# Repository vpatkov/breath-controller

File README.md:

# USB-MIDI Breath Controller

A device that converts breath pressure to MIDI data.

The mouthpiece has an adjustable valve for drain control.

The LED's brightness is proportional to the output MIDI value.
Until the USB interface is successfully configured the LED is fully on.

During initialization, the auto-zeroing of the pressure sensor
is performed. So, don't blow into the mouthpiece when
plugging the device.

The mouthpiece and the case are 3D printed from STL files
in the `3d` directory. The silicone tube is 4 mm OD and 2 mm ID.

## Software

By default, the device sends the pressure data as CC2
messages on channel 1, with maximal input and output ranges,
and linear response. These settings can be changed using the
configuration tool (in the `software` directory).

The response curve can be edited by mouse: the left button
adds and drags points, the right button removes them, and the
middle button resets the curve to default. The curve can
be arbitrary.

The input gain is applied before the curve.

Settings can be applied to the device temporary (until power
is removed) or saved permanently (in EEPROM).

The software works on Windows and Linux (both tested), and
should work on macOS.

## Technical details

The device is implemented with ATmega16U4 MCU and
MPXV4006GP pressure sensor. The MCU has hardware USB controller,
ADC, EEPROM, and other peripherals, eliminating the need of additional
chips. In firmware, [LUFA](http://www.lufa-lib.org) USB stack is used.

The pressure is sampled by ADC, averaged for 8 ms, applied auto-zero,
input gain, the response curve, and then is sent to the
host if the value differs from the previously sent one.

The response curve is implemented by a 128-byte lookup table. 
It's simple and allows arbitrary curves.

The runtime configuration is implemented with SysEx messages (see below)
from the host. The configuration tool is written in Python using
[MIDO](https://mido.readthedocs.io) and Tkinter libraries.

### SysEx messages to configure the device

- Set the MIDI channel: `F0 7D 00 XX F7` where `XX` is a MIDI
channel (1..16).

- Set the MIDI message: `F0 7D 01 XX F7` where `XX` is `00` for Control Change,
`01` for Channel Pressure, `02` for Pitch Bend Up, `03` for Pitch Bend Down.

- Set the control number: `F0 7D 02 XX F7` where `XX` is a control number (0..127).

- Set the input gain: `F0 7D 03 XX F7` where `XX` is input gain multiplied
by 10. `XX` must be in range 10..40.

- Set the response curve: `F0 7D 04 X0 X1 ... X127 F7` where
`X0 X1 ... X127` is a 128-byte lookup table. Each `Xn` must be in the range 0..127.

- Save current settings to EEPROM: `F0 7D 05 F7`.

### Preset file format

Presets used by the configuration tool are just plain text files
containing following lines:

- `midi_channel` followed by a decimal number (1..16);
- `midi_message` followed by a `control_change`, `channel_pressure`, `pitch_bend_up`,
or `pitch_bend_down`;
- `control_number` followed by a decimal number (0..127);
- `input_gain` followed by a floating point decimal number
(between 1.0 and 4.0);
- `curve` followed by a space delimited list of points `(x,y)`
where `x` and `y` are decimal numbers (0..127), assuming
linear interpolation between the points.

You can ignore some of the settings, they will not changed after loading the
preset. For example, you can create curve-only presets.

Preset must have `.preset` file extension and lie in the
`software/presets` directory.

## Programming

ATmega16U4-AU is shipped with a pre-installed USB bootloader and can be
programmed with the official
[FLIP](https://www.microchip.com/DevelopmentTools/ProductDetails/PartNO/FLIP)
software or [dfu-programmer](https://dfu-programmer.github.io/). To enter the
bootloader short HWB pin to GND during reset (there are screwdriver-compatible
pads for that on the PCB). Just in case, the PCB has pogo-compatible pads for
ISP programming. The fuses are factory default.

## License

Unless otherwise noted, this work is licensed under Creative Commons Zero 1.0.

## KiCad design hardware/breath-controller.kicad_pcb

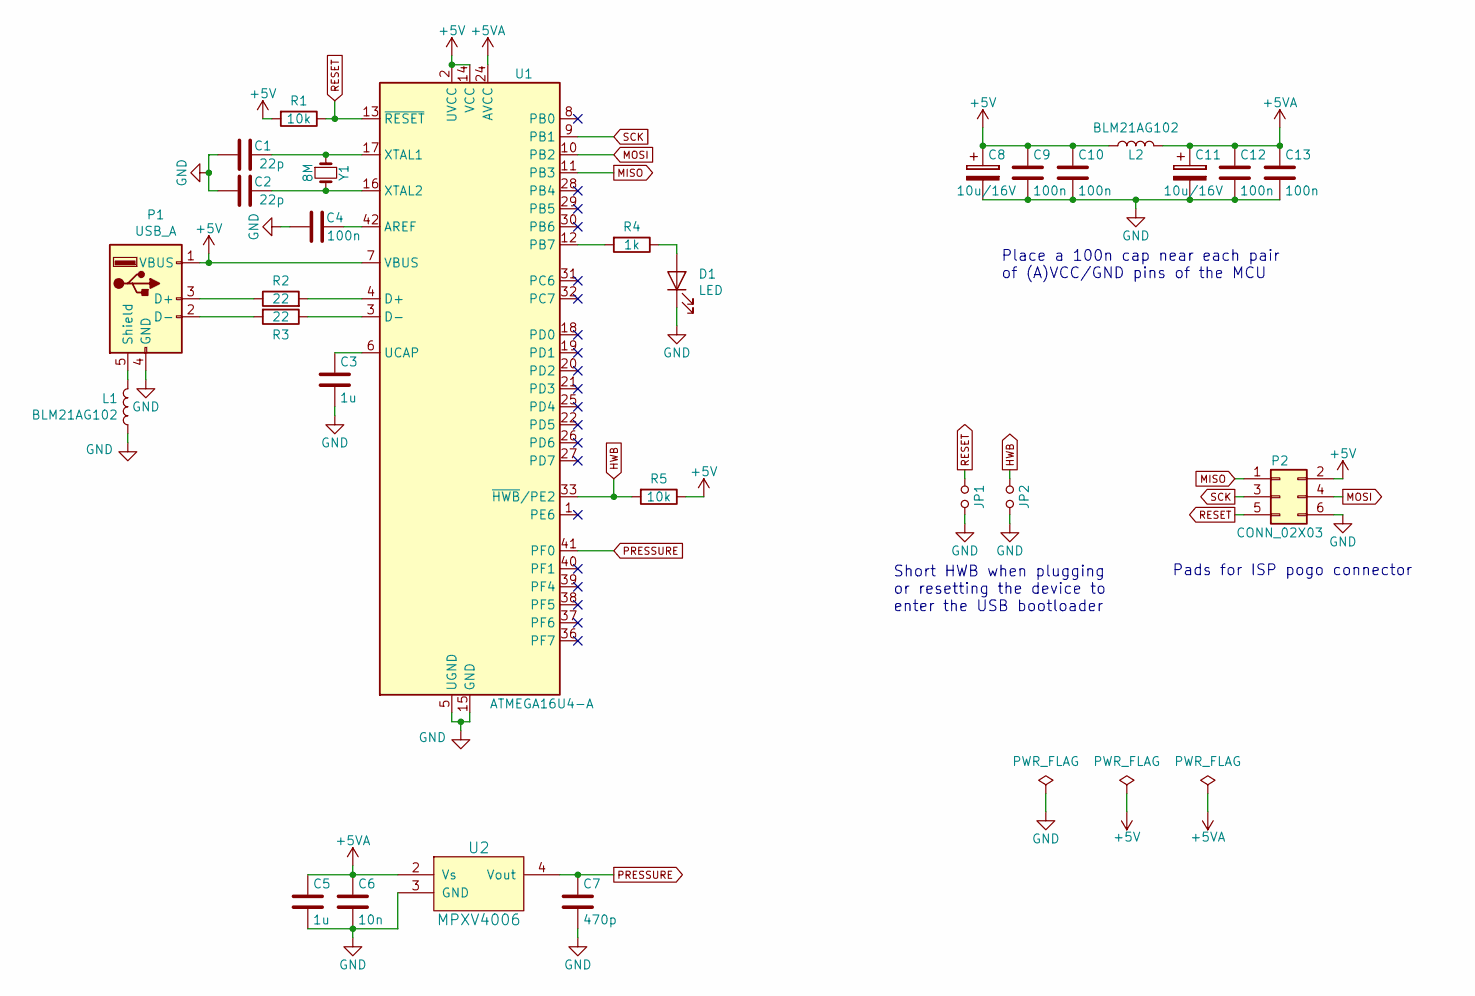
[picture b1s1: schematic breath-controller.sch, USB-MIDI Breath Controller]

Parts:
C1, C2: 22p; C_0805
C3, C5: 1u; C_0805
C4, C9, C10, C12, C13: 100n; C_0805
C6: 10n; C_0805
C7: 470p; C_0805
C8, C11: 10u/16V; c_elec_4x5.3
D1: LED; LED_2X5
JP1, JP2: Jumper_NO_Small; JUMPER_PADS
L1, L2: BLM21AG102; R_0805
P1: USB_A; USB_A_4UCON_10016
P2: CONN_02X03; POGO_AVR_ISP6
R1, R5: 10k; R_0805
R2, R3: 22; R_0805
R4: 1k; R_0805
U1: ATMEGA16U4-A; TQFP-44_10x10mm_Pitch0.8mm
U2: MPXV4006; MPXV4006GP
Y1: 8M; CRYSTAL_5032_2PIN

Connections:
+5V: C8.1, C9.1, C10.1, L2.1, P1.1 (VBUS), P2.2, R1.2, R5.1, U1.2 (UVCC), U1.7 (VBUS), U1.14 (VCC), U1.34 (VCC)
+5VA: C5.1, C6.1, C11.1, C12.1, C13.1, L2.2, U1.24 (AVCC), U1.44 (AVCC), U2.2 (Vs)
GND: C1.2, C2.2, C3.2, C4.2, C5.2, C6.2, C7.2, C8.2, C9.2, C10.2, C11.2, C12.2, C13.2, D1.1 (K), JP1.2, JP2.2, L1.1, P1.4 (GND), P2.6, U1.5 (UGND), U1.15 (GND), U1.23 (GND), U1.35 (GND), U1.43 (GND), U2.3 (GND)
HWB: JP2.1, R5.2, U1.33 (~HWB~/PE2)
MISO: P2.1, U1.11 (PB3)
MOSI: P2.4, U1.10 (PB2)
unnamed: C1.1, U1.17 (XTAL1), Y1.1
unnamed: C2.1, U1.16 (XTAL2), Y1.2
unnamed: C3.1, U1.6 (UCAP)
unnamed: C4.1, U1.42 (AREF)
unnamed: D1.2 (A), R4.1
unnamed: L1.2, P1.5 (Shield)
unnamed: P1.2 (D-), R3.2
unnamed: P1.3 (D+), R2.1
unnamed: R2.2, U1.4 (D+)
unnamed: R3.1, U1.3 (D-)
unnamed: R4.2, U1.12 (PB7)
PRESSURE: C7.1, U1.41 (PF0), U2.4 (Vout)
RESET: JP1.1, P2.5, R1.1, U1.13 (~RESET)
SCK: P2.3, U1.9 (PB1)

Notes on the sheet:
Place a 100n cap near each pair of (A)VCC/GND pins of the MCU
Pads for ISP pogo connector
Short HWB when plugging or resetting the device to enter the USB bootloader

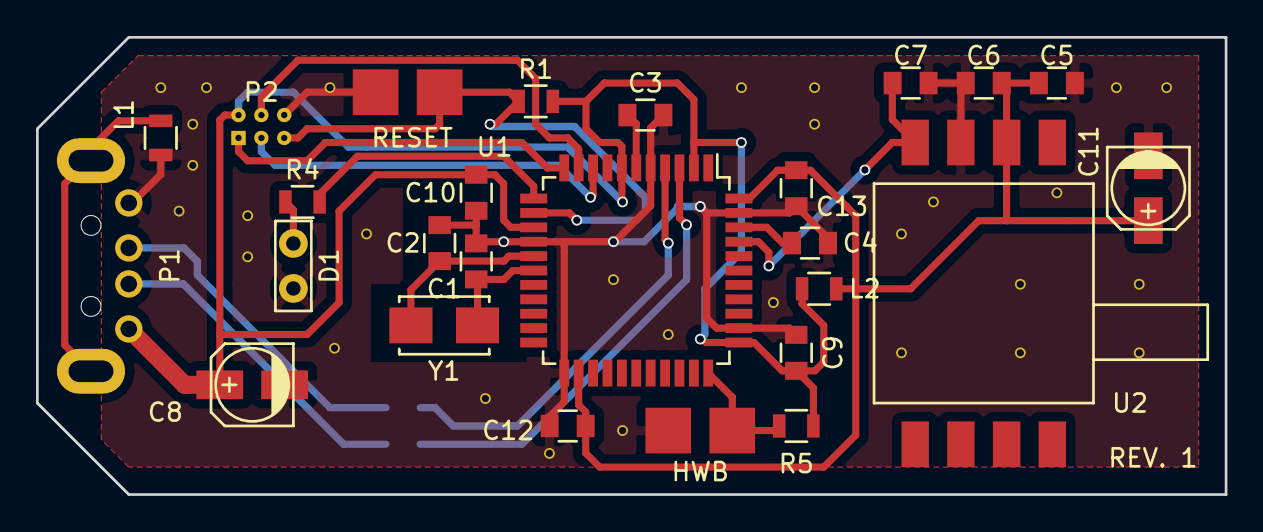
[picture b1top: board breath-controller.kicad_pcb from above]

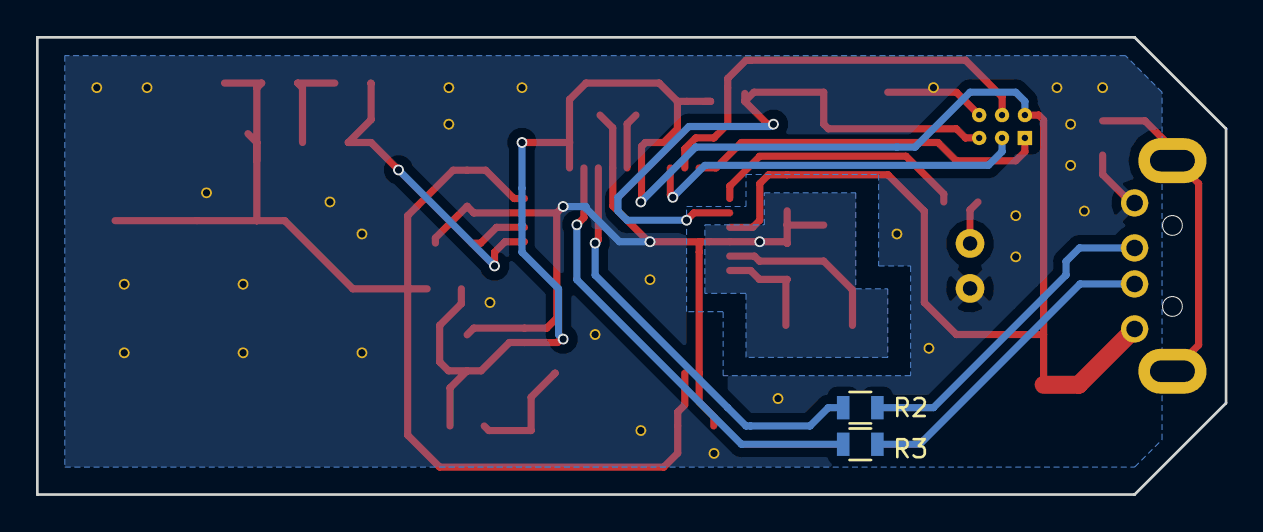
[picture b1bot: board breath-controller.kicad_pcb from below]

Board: 2 copper layers, 66.0 x 25.4 mm, 28 parts (2 on the bottom side), 20 nets.
